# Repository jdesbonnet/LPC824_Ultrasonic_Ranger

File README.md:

# LPC824_Ultrasonic_Ranger

This is a sonar sensor comprising a LPC824 ARM Cortex M0+ MCU, low cost 40kHz ultrasonic transducers and opamps. The firmware
uses the LPC824 ADC DMA (direct memory access) capability to read analog samples at high speed into SRAM.

Unlike many ranging sensors that output just distance to target, this project is 
designed to capture the entire echo of an ultrasonic 'ping'. Potential uses include
measuring agricultural crop yield. 

## Frequency response of low cost 40kHz transducer

Method: a transmitter and transducer are taped together (separation distance 0).
An oscilloscope (Keysight DSO-X 3014A) waveform generator is set to 5V peak-to-peak 
sine wave, and the receiver is connected to a channel on oscilloscope set to 2V 
per division.  The frequency is varied around 40kHz using waveform generator menu. 
Only one device pair was tested. 

Observation: useful bandwidth is only 1kHz centered at about 40.5kHz. 

Pulse (yellow) and echo (green) on oscilloscope:

## LPC824 pin utilization

|Pin| Function|                      |Pin | Function |                 |
|---| --------| ---------------------|--- |----------|-----------------|
| 1 | ADC3    | RX amp out           | 20 | PIO_0_14 | Debug pin       |
| 2 | ADC9    | 2nd stage RX amp out | 19 | PIO0_0   | UART RXD        |
| 3 | PIO0_13 | nc                   | 18 | VrefP    | tied to 3.3V    |
| 4 | PIO0_12 | nc                   | 17 | VrefN    | tied to GND     |
| 5 | RESET   | SWD reset            | 16 | Vss      |                 |
| 6 | PIO0_4  | UART TXD             | 15 | Vdd      |                 |
| 7 | SWCLK   | SWD clock            | 14 | PIO0_8   | nc              |
| 8 | SWDIO   | SWD data             | 13 | PIO0_9   | Transducer TX_B |
| 9 | PIO0_11 | nc                   | 12 | PIO0_1   | nc              |
|10 | PIO0_10 | nc                   | 11 | PIO0_15  | Transducer TX_A |

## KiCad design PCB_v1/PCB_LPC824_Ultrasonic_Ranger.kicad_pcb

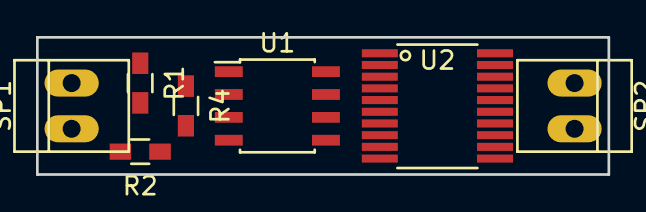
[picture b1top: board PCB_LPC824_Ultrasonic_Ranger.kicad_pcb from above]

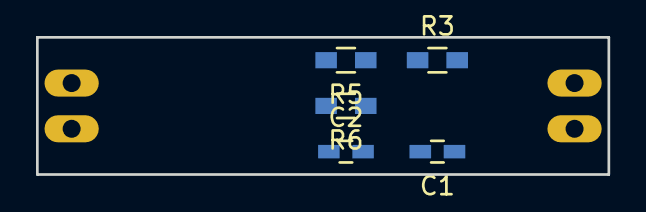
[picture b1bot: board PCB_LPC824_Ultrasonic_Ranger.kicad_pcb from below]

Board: 2 copper layers, 31.8 x 7.6 mm, 12 parts (5 on the bottom side), 11 nets, no tracks yet.

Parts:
C1, C2: C; C_0603_HandSoldering
R1, R2, R3, R4, R5, R6: R; R_0603_HandSoldering
SP1, SP2: SPEAKER; PINHEAD1-2
U1: OP275; SOIC-8_3.9x4.9mm_Pitch1.27mm
U2: LPC824M201JDH20; TSSOP-20_4.4x6.5mm_Pitch0.65mm

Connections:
+3V3: R1.1, U1.8, U2.15, U2.18
ADC3: R3.1, U1.1, U1.5, U2.1
ADC9: R5.1, U1.7, U2.2
GND: C1.2, C2.2, R2.2, SP1.1, U1.4, U2.16, U2.17
unnamed: C1.1, R4.2
unnamed: C2.1, R6.2
unnamed: R1.2, R2.1, SP1.2, U1.3
unnamed: R3.2, R4.1, U1.2
unnamed: R5.2, R6.1, U1.6
TX_A: SP2.2, U2.10
TX_B: SP2.1, U2.9

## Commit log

2017-01-22 start with ADC DMA example
2017-01-23 pulse 40kHz transducer, output ADC and repeat
2017-01-23 move setup code into functions
2017-01-23 output echogram in Base64 for higher throughput
2017-01-23 prefix data lines with header
2017-01-25 frequency response of low cost 40kHz transducer
2017-01-25 frequency response curve
2017-01-25 no comment
2017-01-25 use SCT to drive transducer
2017-01-25 tidy
2017-01-25 add scope trace
2017-01-25 crop scope trace
2017-01-25 update comments
2017-02-04 pin assignments
2017-02-04 update pin assignments
2018-04-26 diable internal pullup on ADC input
2018-04-26 schematic of prototype analog amp
2018-04-27 schematic
2018-05-16 start PCB
2026-03-16 Update UART pin description in README
2026-03-16 Fix LPC824 pin utilization table formatting
